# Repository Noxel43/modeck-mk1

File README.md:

# modeck. mk1

*A fully open-source, DIY MP3 Player*

## Core Features:
- Loads of buttons (9) that are each mappable
- ~~Lovely tactile feel~~ (I lie, currently, for prototyping, I'm just using 6mm tacts, however, I really want to incorporate keyboard switches)
- Physical EQ. A potentiometer (currently twist, but I will make it slide) that controls the EQ
- Colour LCD screen (170x320 res)
- USB-C charging (I plan to incorporate pogo pins on the back)
- SD card for storage - easily transfer songs
- Stereo audio (why am I mentioning this, who wants a mono mp3 player?)
- 2 Layer PCB. The PCB consists of only two layers, so its cheap to produce.
- Possible WiFi/BT. For the PCB, I am using the [ESP32-S3-WROOM-1](https://www.altronics.com.au/product/z6433-esp-32s3-development-board), which has WiFi and a built in atenna. It's not currently a priority, but streaming, or at least downloading from wifi would be cool.

## Core Components:
***Note:** This is the list of* main *components, not a full BOM, which can be found [here](BOM.csv).*
- [ESP32-S3-WROOM-1](https://www.altronics.com.au/product/z6433-esp-32s3-development-board)
  - This is the main MCU, i.e. the brains
- [ES8388](http://lcsc.com/product-detail/C365736.html)
  - This is the audio codec, handling all of the audio output
- [Waveshare 1.9" LCD screen, SKU: 23822](https://www.waveshare.com/1.9inch-lcd-module.htm)
  - Used as the screen (duh). Can be substituted for any 1.9" screen.
- [Battery](https://www.youtube.com/watch?v=dQw4w9WgXcQ&list=RDdQw4w9WgXcQ&start_radio=1)
  - I'm writing this on my school laptop and I can't remember what I'm using specifically, but it's a LiPo. Watch this spot.

## Specifications:

placeholder

## Timeline:

#### **Current Phase:** Prototyping & EVT

*making sure everything works, not yet usable by public*
***Timeframe:** next month or two*

**Current:** PCB design done

**Next:**
- [ ] Make basic firmware for audio playback only
- [ ] Add input handling for all buttons
- [ ] Add a GUI for the screens
- [ ] Add EQ

#### **Next Phase:** DVT & Release

*design validation test, i.e. adding the case, etc*
***Timeframe (from phase start):** ~1 month*

- [ ] Create enclosure
- [ ] Ensure easy printability and assembly
- [ ] Publish v1 with guides, etc, ready without a polished firmware, if people want to make their own.
- [ ] Polish firmware, add different modes, and a good UI/UX
- [ ] Release full.

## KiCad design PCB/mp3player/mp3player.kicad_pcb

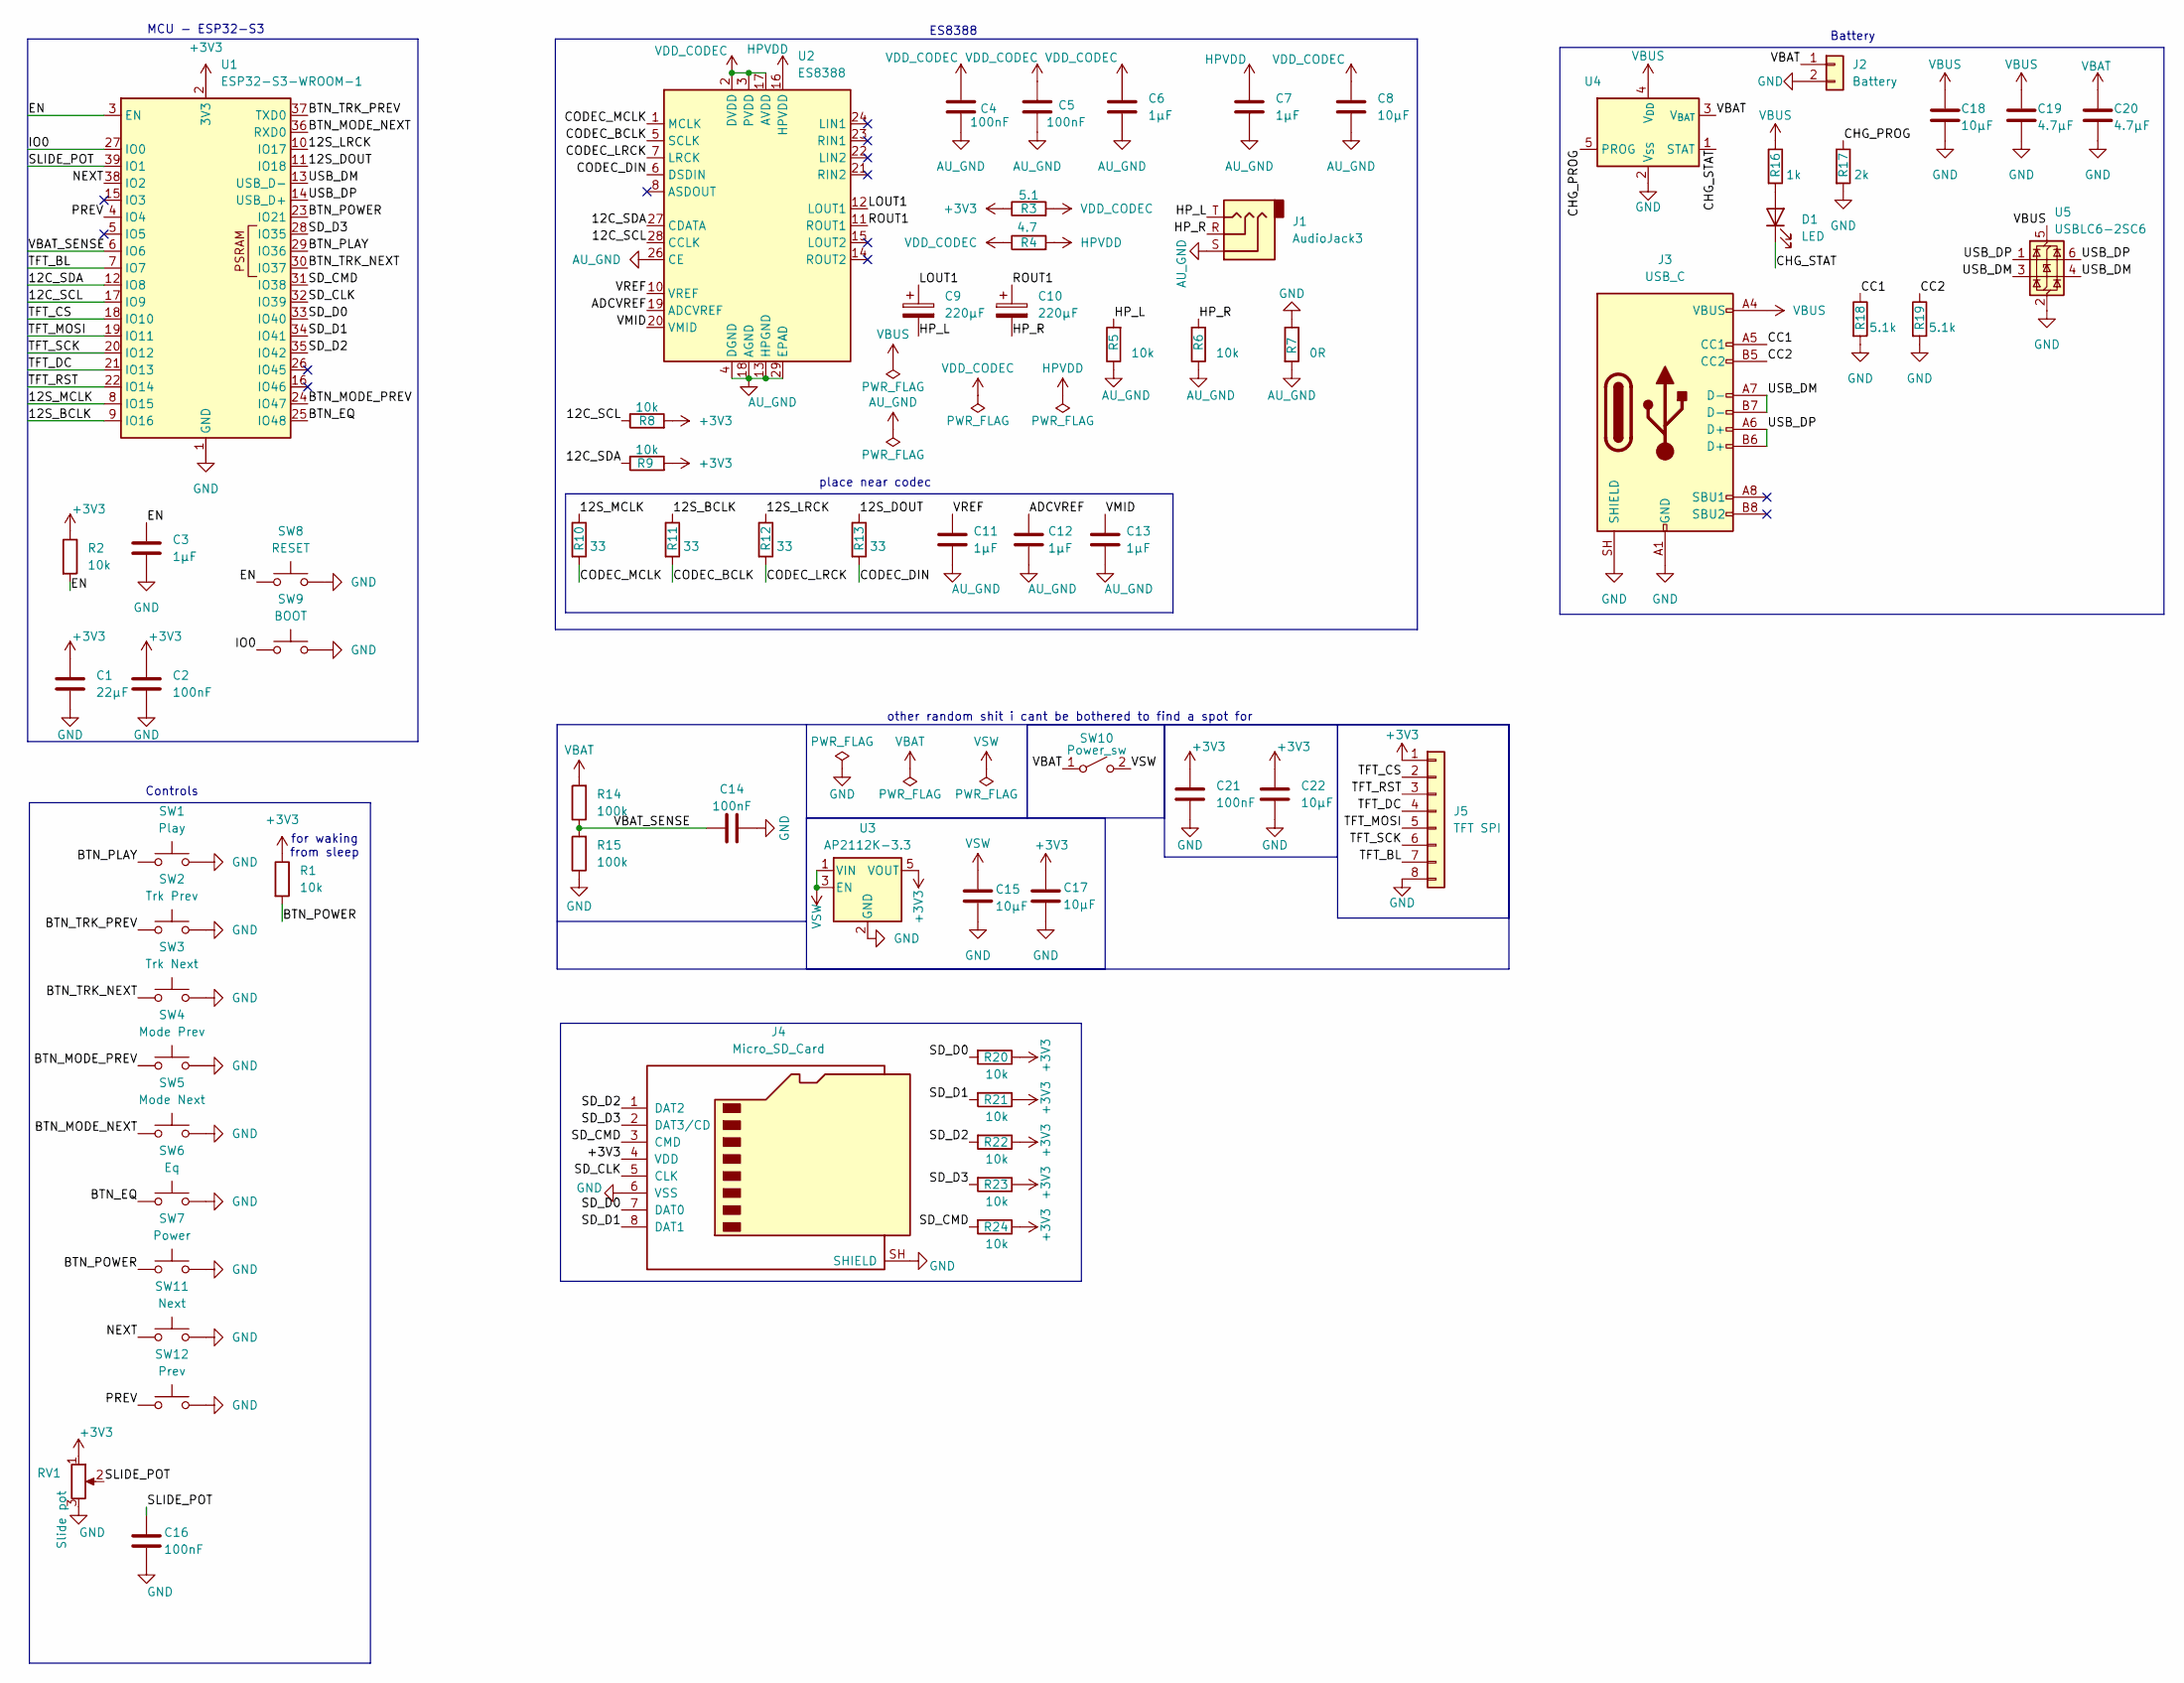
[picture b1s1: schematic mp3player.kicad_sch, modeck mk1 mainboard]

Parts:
C1: 22μF; C_0805_2012Metric
C2, C4, C5, C14, C16, C21: 100nF; C_0603_1608Metric
C3, C6, C7, C11, C12, C13: 1μF; C_0603_1608Metric
C8, C15, C17, C18, C22: 10μF; C_0805_2012Metric
C9, C10: 220μF; CP_Elec_6.3x5.4
C19, C20: 4.7μF; C_0805_2012Metric
D1: LED; LED_0603_1608Metric
J1: AudioJack3; Jack_3.5mm_CUI_SJ-3523-SMT_Horizontal
J2: Battery; PinSocket_1x02_P2.00mm_Horizontal
J3: USB_C; USB_C_Receptacle_Amphenol_124019772112A
J4: Micro_SD_Card; microSD_HC_Wuerth_693072010801
J5: TFT SPI; JST_GH_SM08B-GHS-TB_1x08-1MP_P1.25mm_Horizontal
R1, R2, R5, R6, R8, R9, R20, R21, R22, R23, R24: 10k; R_0603_1608Metric
R3: 5.1; R_0603_1608Metric
R4: 4.7; R_0603_1608Metric
R7: 0R; R_0603_1608Metric
R10, R11, R12, R13: 33; R_0603_1608Metric
R14, R15: 100k; R_0603_1608Metric
R16: 1k; R_0603_1608Metric
R17: 2k; R_0603_1608Metric
R18, R19: 5.1k; R_0603_1608Metric
RV1: Slide pot; Potentiometer_ACP_CA6-VSMD_Vertical
SW1: Play; SW_PUSH_6mm_H4.3mm
SW2: Trk Prev; SW_PUSH_6mm_H4.3mm
SW3: Trk Next; SW_PUSH_6mm_H4.3mm
SW4: Mode Prev; SW_PUSH_6mm_H4.3mm
SW5: Mode Next; SW_PUSH_6mm_H4.3mm
SW6: Eq; SW_PUSH_6mm_H4.3mm
SW7: Power; SW_PUSH_6mm_H4.3mm
SW8: RESET; SW_SPST_PTS810
SW9: BOOT; SW_SPST_PTS810
SW10: Power_sw; SW_DIP_SPSTx01_Slide_6.7x4.1mm_W6.73mm_P2.54mm_LowProfile_J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
SW11: Next; SW_PUSH_6mm_H4.3mm
SW12: Prev; SW_PUSH_6mm_H4.3mm
U1: ESP32-S3-WROOM-1
U2: ES8388; QFN-28-1EP_4x4mm_P0.45mm_EP2.6x2.6mm
U3: AP2112K-3.3; SOT-23-5
U4: MCP73831-2-OT; SOT-23-5
U5: USBLC6-2SC6; SOT-23-6

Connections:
+3V3: C1.1, C2.1, C17.1, C21.1, C22.1, J4.4 (VDD), J5.1, R1.1, R2.1, R3.1, R8.2, R9.2, R20.1, R21.1, R22.1, R23.1, R24.1, RV1.1, U1.2 (3V3), U3.5 (VOUT)
/12C_SCL: R8.1, U1.17 (IO9), U2.28 (CCLK)
/12C_SDA: R9.1, U1.12 (IO8), U2.27 (CDATA)
/12S_BCLK: R11.1, U1.9 (IO16)
/12S_DOUT: R13.1, U1.11 (IO18)
/12S_LRCK: R12.1, U1.10 (IO17)
/12S_MCLK: R10.1, U1.8 (IO15)
/ADCVREF: C12.1, U2.19 (ADCVREF)
/BTN_EQ: SW6.1, U1.25 (IO48)
/BTN_MODE_NEXT: SW5.1, U1.36 (RXD0)
/BTN_MODE_PREV: SW4.1, U1.24 (IO47)
/BTN_PLAY: SW1.1, U1.29 (IO36)
/BTN_POWER: R1.2, SW7.1, U1.23 (IO21)
/BTN_TRK_NEXT: SW3.1, U1.30 (IO37)
/BTN_TRK_PREV: SW2.1, U1.37 (TXD0)
/CC1: J3.A5 (CC1), R18.1
/CC2: J3.B5 (CC2), R19.1
/CHG_PROG: R17.1, U4.5 (PROG)
/CHG_STAT: D1.1 (K), U4.1 (STAT)
/CODEC_BCLK: R11.2, U2.5 (SCLK)
/CODEC_DIN: R13.2, U2.6 (DSDIN)
/CODEC_LRCK: R12.2, U2.7 (LRCK)
/CODEC_MCLK: R10.2, U2.1 (MCLK)
/EN: C3.1, R2.2, SW8.1, U1.3 (EN)
/HP_L: C9.2, J1.T, R5.2
/HP_R: C10.2, J1.R, R6.2
/IO0: SW9.1, U1.27 (IO0)
/LOUT1: C9.1, U2.12 (LOUT1)
/NEXT: SW11.1, U1.38 (IO2)
/PREV: SW12.1, U1.4 (IO4)
/ROUT1: C10.1, U2.11 (ROUT1)
/SD_CLK: J4.5 (CLK), U1.32 (IO39)
/SD_CMD: J4.3 (CMD), R24.2, U1.31 (IO38)
/SD_D0: J4.7 (DAT0), R20.2, U1.33 (IO40)
/SD_D1: J4.8 (DAT1), R21.2, U1.34 (IO41)
/SD_D2: J4.1 (DAT2), R22.2, U1.35 (IO42)
/SD_D3: J4.2 (DAT3/CD), R23.2, U1.28 (IO35)
/SLIDE_POT: C16.1, RV1.2, U1.39 (IO1)
/TFT_BL: J5.7, U1.7 (IO7)
/TFT_CS: J5.2, U1.18 (IO10)
/TFT_DC: J5.4, U1.21 (IO13)
/TFT_MOSI: J5.5, U1.19 (IO11)
/TFT_RST: J5.3, U1.22 (IO14)
/TFT_SCK: J5.6, U1.20 (IO12)
/USB_DM: J3.A7 (D-), J3.B7 (D-), U1.13 (USB_D-), U5.3 (I/O2), U5.4 (I/O2)
/USB_DP: J3.A6 (D+), J3.B6 (D+), U1.14 (USB_D+), U5.1 (I/O1), U5.6 (I/O1)
/VBAT_SENSE: C14.1, R14.1, R15.2, U1.6 (IO6)
/VMID: C13.1, U2.20 (VMID)
/VREF: C11.1, U2.10 (VREF)
AU_GND: C4.2, C5.2, C6.2, C7.2, C8.2, C11.2, C12.2, C13.2, J1.S, R5.1, R6.1, R7.2, U2.4 (DGND), U2.13 (HPGND), U2.18 (AGND), U2.26 (CE), U2.29 (EPAD)
GND: C1.2, C2.2, C3.2, C14.2, C15.2, C16.2, C17.2, C18.2, C19.2, C20.2, C21.2, C22.2, J2.2, J3.A1 (GND), J3.A12 (GND), J3.B1 (GND), J3.B12 (GND), J3.SH (SHIELD), J4.6 (VSS), J4.SH (SHIELD), J5.8, R7.1, R15.1, R17.2, R18.2, R19.2, RV1.3, SW1.2, SW2.2, SW3.2, SW4.2, SW5.2, SW6.2, SW7.2, SW8.2, SW9.2, SW11.2, SW12.2, U1.1 (GND), U1.40 (GND), U1.41 (GND), U3.2 (GND), U4.2 (V_{SS}), U5.2 (GND)
HPVDD: C7.1, R4.2, U2.16 (HPVDD)
unnamed: D1.2 (A), R16.2
VBAT: C20.1, J2.1, R14.2, SW10.1 (A), U4.3 (V_{BAT})
VBUS: C18.1, C19.1, J3.A4 (VBUS), J3.A9 (VBUS), J3.B4 (VBUS), J3.B9 (VBUS), R16.1, U4.4 (V_{DD}), U5.5 (VBUS)
VDD_CODEC: C4.1, C5.1, C6.1, C8.1, R3.2, R4.1, U2.2 (DVDD), U2.3 (PVDD), U2.17 (AVDD)
VSW: C15.1, SW10.2 (B), U3.1 (VIN), U3.3 (EN)

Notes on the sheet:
Battery
MCU - ESP32-S3
for waking from sleep
ES8388
place near codec
other random shit i cant be bothered to find a spot for
Controls

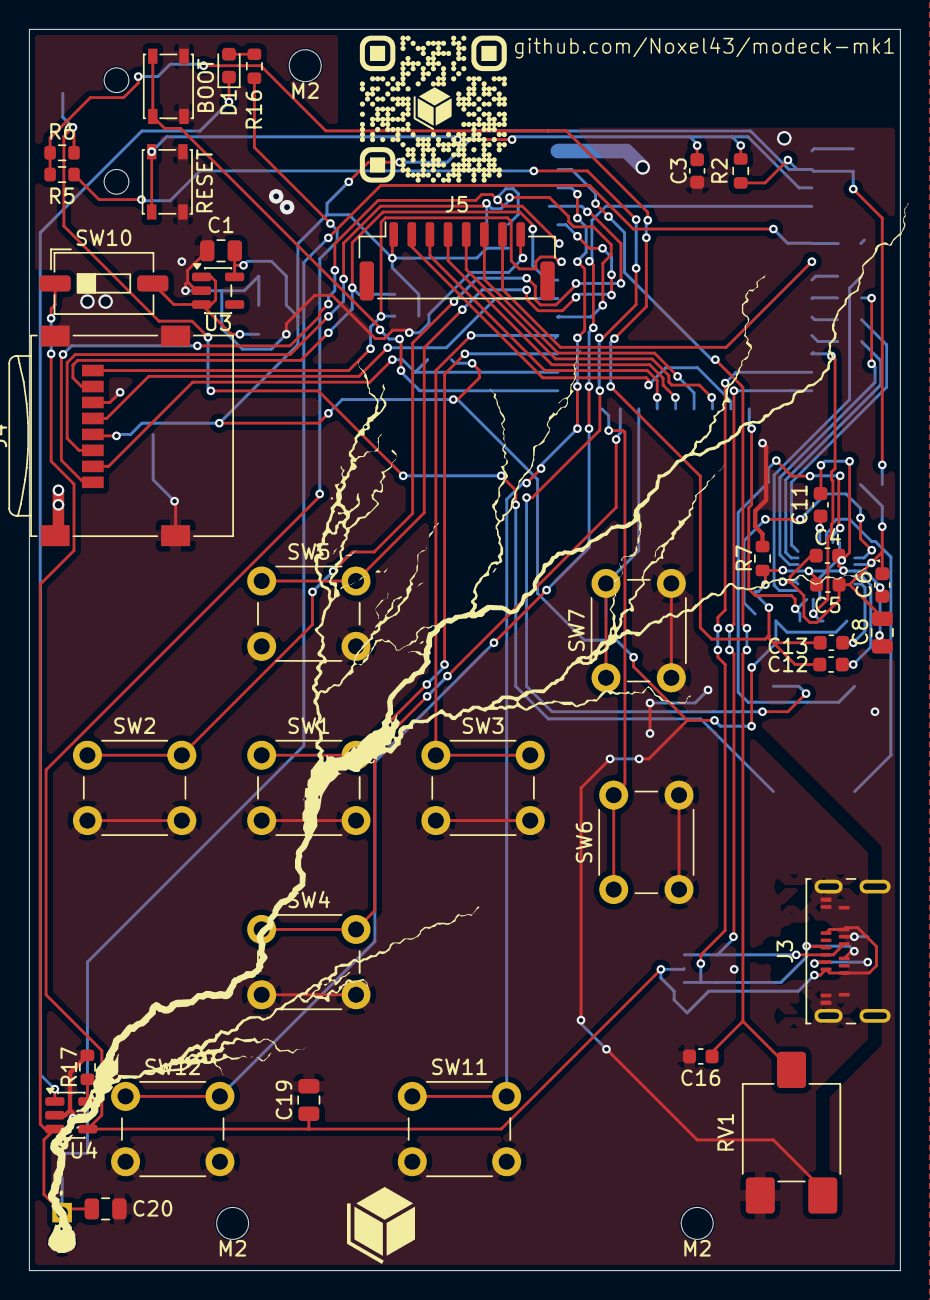
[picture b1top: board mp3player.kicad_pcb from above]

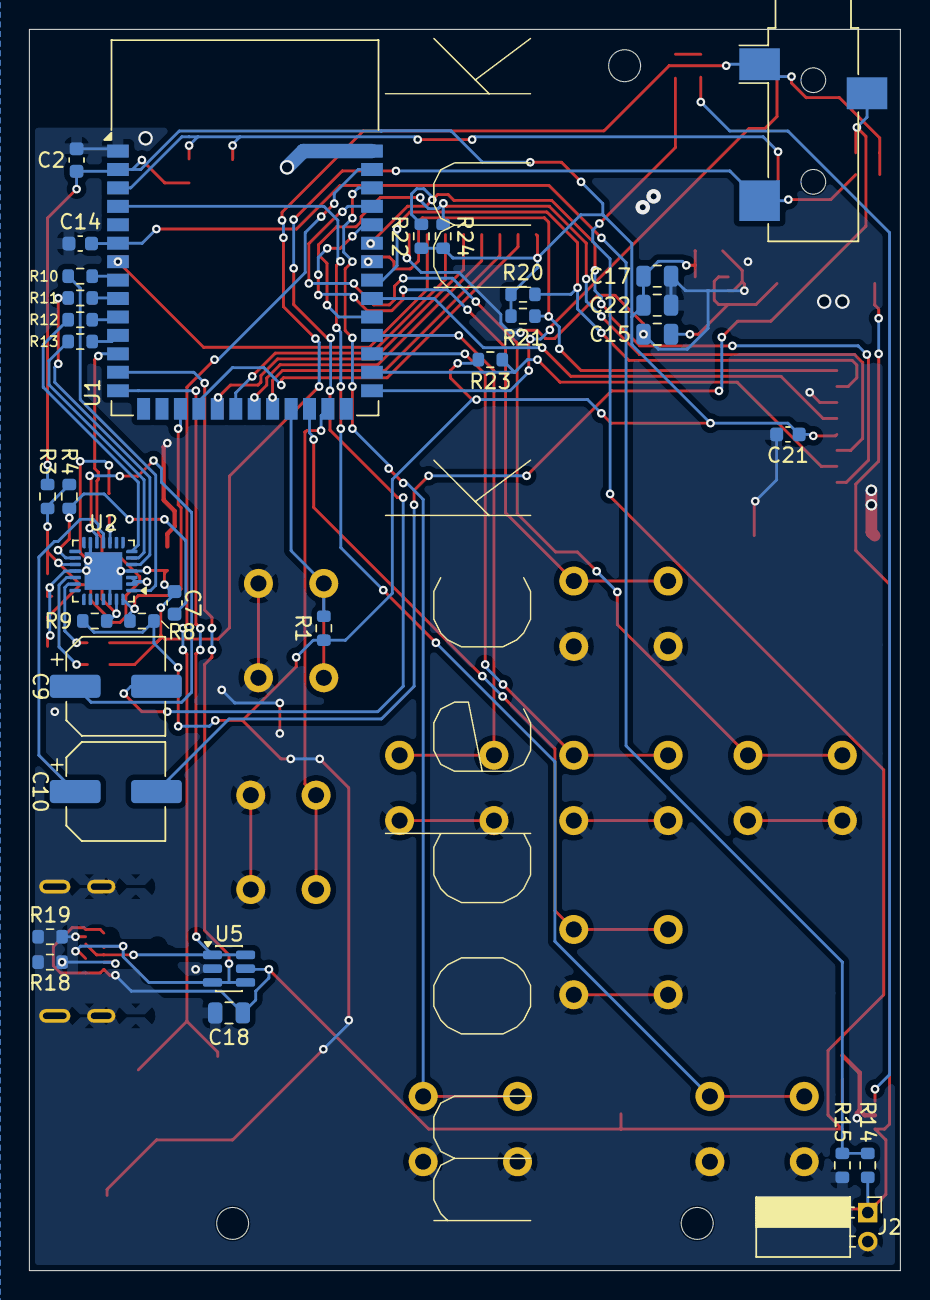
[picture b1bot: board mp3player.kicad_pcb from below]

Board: 2 copper layers, 60.0 x 85.5 mm, 73 parts (33 on the bottom side), 57 nets.

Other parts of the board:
M2, M2#2, M2#3: MountingHole_2.2mm_M2
